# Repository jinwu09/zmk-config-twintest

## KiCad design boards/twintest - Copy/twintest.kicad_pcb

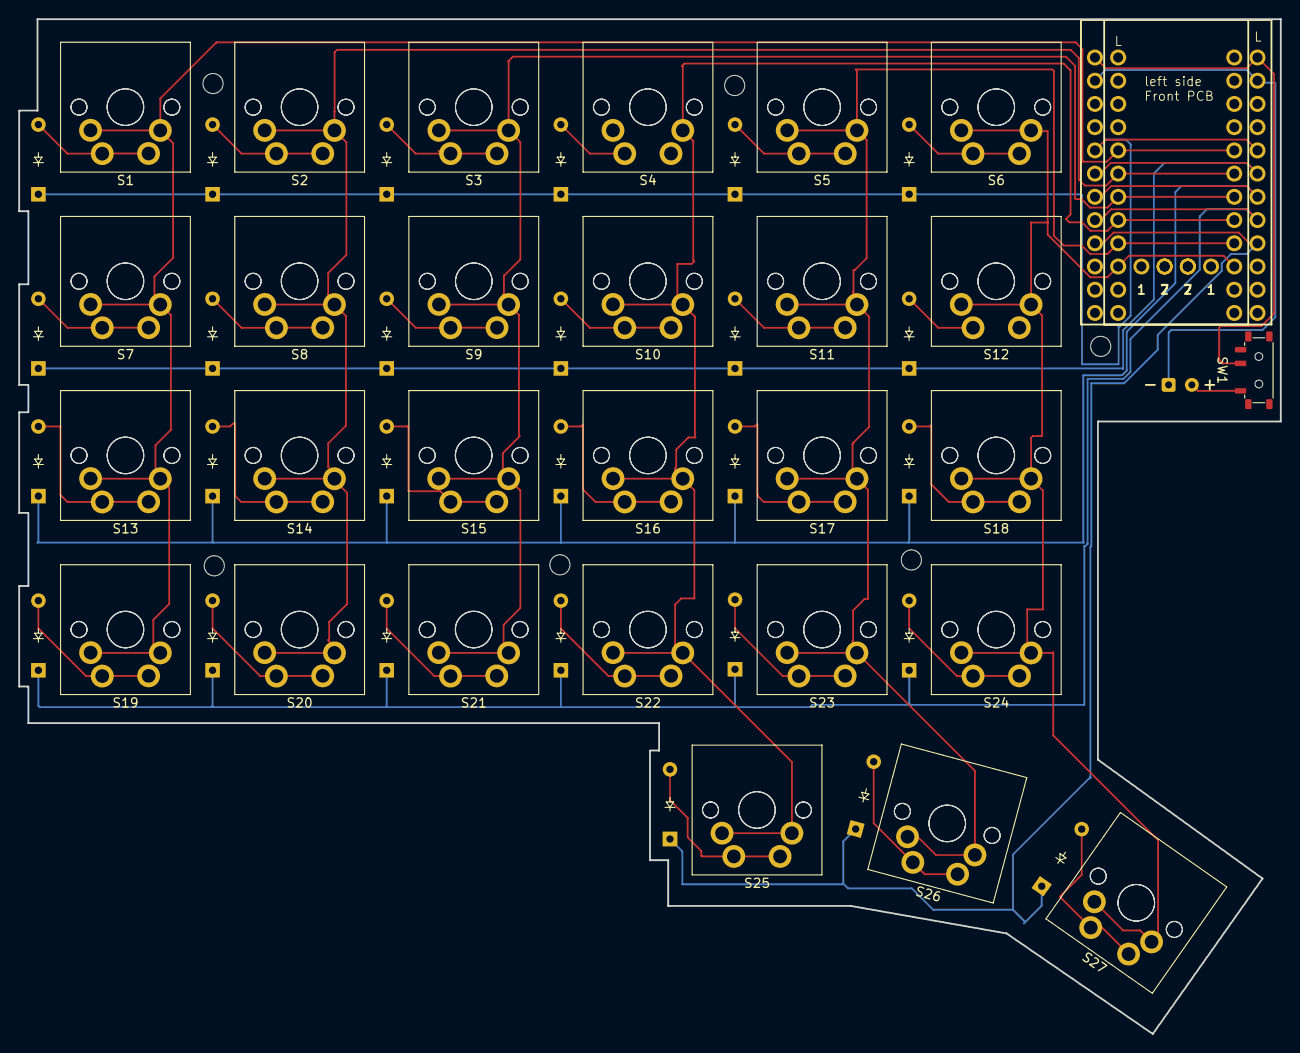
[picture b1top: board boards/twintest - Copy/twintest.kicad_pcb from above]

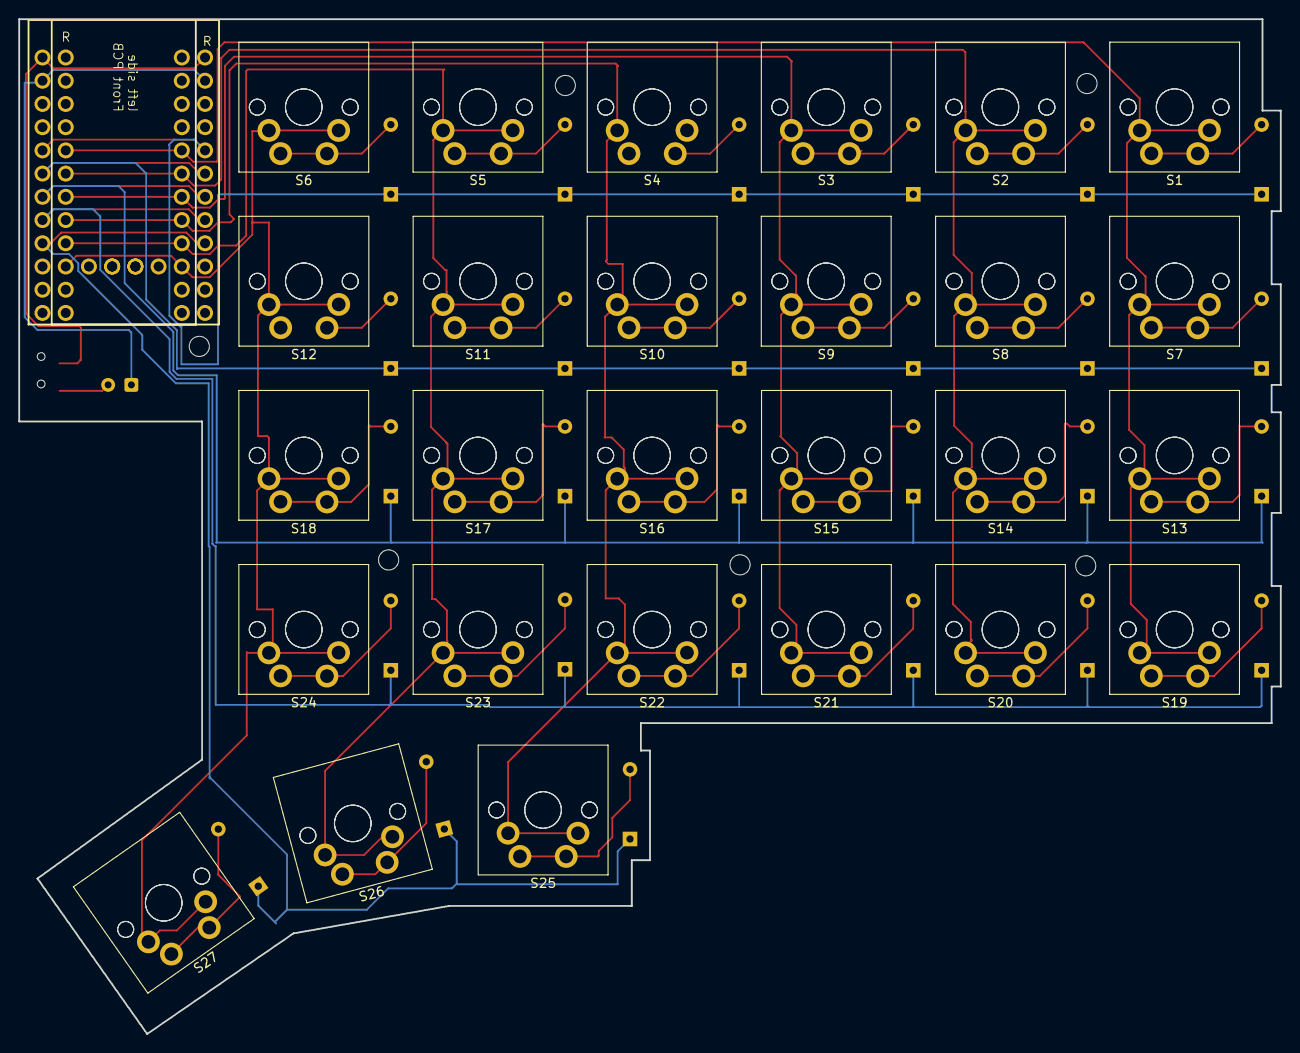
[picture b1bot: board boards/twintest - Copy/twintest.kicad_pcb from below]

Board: 2 copper layers, 138.0 x 111.0 mm, 91 parts (28 on the bottom side), 41 nets.

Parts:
BT2: Battery_Cell; Battery
D1, D2, D3, D4, D5, D6, D7, D8, D9, D10, D11, D12, D13, D14, D15, D16, D17, D18, D19, D20, D21, D22, D23, D24, D25, D26, D27: Diode; Diode_DO-35
H1, H2, H3, H4, H5, H6: Mounting_Hole; Standoff_M2x6mm
S1, S1#2, S2, S2#2, S3, S3#2, S4, S4#2, S5, S5#2, S6, S6#2, S7, S7#2, S8, S8#2, S9, S9#2, S10, S10#2, S11, S11#2, S12, S12#2, S13, S13#2, S14, S14#2, S15, S15#2, S16, S16#2, S17, S17#2, S18, S18#2, S19, S19#2, S20, S20#2, S21, S21#2, S22, S22#2, S23, S23#2, S24, S24#2, S25, S25#2, S26, S26#2, S27, S27#2: Keyswitch; MX_PCB_1.00u
SW1: Switch; Switch_MSK12C02
U1, U2: Nice_Nano_V2

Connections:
unnamed: BT2.1 (+), SW1.2
unnamed: D1.2 (A), S1.2, S1#2.2
unnamed: D2.2 (A), S2.2, S2#2.2
unnamed: D3.2 (A), S3.2, S3#2.2
unnamed: D4.2 (A), S4.2, S4#2.2
unnamed: D5.2 (A), S5.2, S5#2.2
unnamed: D6.2 (A), S6.2, S6#2.2
unnamed: D7.2 (A), S7.2, S7#2.2
unnamed: D8.2 (A), S8.2, S8#2.2
unnamed: D9.2 (A), S9.2, S9#2.2
unnamed: D10.2 (A), S10.2, S10#2.2
unnamed: D11.2 (A), S11.2, S11#2.2
unnamed: D12.2 (A), S12.2, S12#2.2
unnamed: D13.2 (A), S13.2, S13#2.2
unnamed: D14.2 (A), S14.2, S14#2.2
unnamed: D15.2 (A), S15.2, S15#2.2
unnamed: D16.2 (A), S16.2, S16#2.2
unnamed: D17.2 (A), S17.2, S17#2.2
unnamed: D18.2 (A), S18.2, S18#2.2
unnamed: D19.2 (A), S19.2, S19#2.2
unnamed: D20.2 (A), S20.2, S20#2.2
unnamed: D21.2 (A), S21.2, S21#2.2
unnamed: D22.2 (A), S22.2, S22#2.2
unnamed: D23.2 (A), S23.2, S23#2.2
unnamed: D24.2 (A), S24.2, S24#2.2
unnamed: D25.2 (A), S25.2, S25#2.2
unnamed: D26.2 (A), S26.2, S26#2.2
unnamed: D27.2 (A), S27.2, S27#2.2
battery +: SW1.1, U1.24 (B+), U2.24 (B+)
battery -: BT2.2 (-), U1.23 (GND), U2.23 (GND)
collumn 1: S1.1, S1#2.1, S7.1, S7#2.1, S13.1, S13#2.1, S19.1, S19#2.1, U1.5 (2), U2.5 (2)
collumn 2: S2.1, S2#2.1, S8.1, S8#2.1, S14.1, S14#2.1, S20.1, S20#2.1, U1.6 (3), U2.6 (3)
collumn 3: S3.1, S3#2.1, S9.1, S9#2.1, S15.1, S15#2.1, S21.1, S21#2.1, U1.7 (4), U2.7 (4)
collumn 4: S4.1, S4#2.1, S10.1, S10#2.1, S16.1, S16#2.1, S22.1, S22#2.1, S25.1, S25#2.1, U1.8 (5), U2.8 (5)
collumn 5: S5.1, S5#2.1, S11.1, S11#2.1, S17.1, S17#2.1, S23.1, S23#2.1, S26.1, S26#2.1, U1.9 (6), U2.9 (6)
collumn 6: S6.1, S6#2.1, S12.1, S12#2.1, S18.1, S18#2.1, S24.1, S24#2.1, S27.1, S27#2.1, U1.10 (7), U2.10 (7)
row 1: D1.1 (K), D2.1 (K), D3.1 (K), D4.1 (K), D5.1 (K), D6.1 (K), U1.20 (21), U2.20 (21)
row 2: D7.1 (K), D8.1 (K), D9.1 (K), D10.1 (K), D11.1 (K), D12.1 (K), U1.19 (20), U2.19 (20)
row 3: D13.1 (K), D14.1 (K), D15.1 (K), D16.1 (K), D17.1 (K), D18.1 (K), U1.18 (19), U2.18 (19)
row 4: D19.1 (K), D20.1 (K), D21.1 (K), D22.1 (K), D23.1 (K), D24.1 (K), U1.17 (18), U2.17 (18)
row 5: D25.1 (K), D26.1 (K), D27.1 (K), U1.16 (15), U2.16 (15)

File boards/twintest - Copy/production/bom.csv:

Designator,Footprint,Quantity,Value,LCSC Part #
BT2,Battery,1,Battery_Cell,
"D1, D10, D11, D12, D13, D14, D15, D16, D17, D18, D19, D2, D20, D21, D22, D23, D24, D25, D26, D27, D3, D4, D5, D6, D7, D8, D9",Diode_DO-35,27,Diode,
"H1, H2, H3, H4, H5, H6",Standoff_M2x6mm,6,Mounting_Hole,
"S1_2, S1, S10_2, S10, S11_2, S11, S12_2, S12, S13_2, S13, S14_2, S14, S15_2, S15, S16_2, S16, S17_2, S17, S18_2, S18, S19_2, S19, S2_2, S2, S20_2, S20, S21_2, S21, S22_2, S22, S23_2, S23, S24_2, S24, S25_2, S25, S26_2, S26, S27_2, S27, S3_2, S3, S4_2, S4, S5_2, S5, S6_2, S6, S7_2, S7, S8_2, S8, S9_2, S9",MX_PCB_1.00u,54,Keyswitch,
SW1,Switch_MSK12C02,1,Switch,
"U1, U2",Nice_Nano_V2,2,Nice_Nano_V2,

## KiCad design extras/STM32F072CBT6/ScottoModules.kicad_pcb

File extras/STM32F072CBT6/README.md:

# ScottoModules

Two modules based on the STM32F072CBT6 to make integrated MCU PCBs simpler. They're designed to sit between 2 switches on an ortholinear or row-staggered keyboard, column-staggered will require some manual moving to get them to fit correctly.

# Bill of Materials (BOM)

| Quantity | Part                        | LCSC                                                                               |
| -------- | --------------------------- | ---------------------------------------------------------------------------------- |
| 1        | STM32F072CBT6 (LQFP-48_7x7) | [C81720](https://jlcpcb.com/partdetail/Stmicroelectronics-STM32F072CBT6/C81720)    |
| 1        | XC6206 (SOT-23-3L)          | [C5446](https://jlcpcb.com/partdetail/TorexSemicon-XC6206P332MRG/C5446)            |
| 1        | USBLC6-2SC6 (SOT-23-6)      | [C2827654](https://jlcpcb.com/partdetail/TechPublic-USBLC62SC6/C2827654)           |
| 1        | TL3342                      | [C115351](https://jlcpcb.com/partdetail/Alpsalpine-SKQGABE010/C115351)             |
| 1        | USB_C_HRO_TYPE-C-31-M-12    | [C165948](https://jlcpcb.com/partdetail/Korean_HropartsElec-TYPE_C_31_M12/C165948) |
| 2        | 5.1k Resistor (0402)        | [C25905](https://jlcpcb.com/partdetail/26648-0402WGF5101TCE/C25905)                |
| 1        | 10k Resistor (0402)         | [C25744](https://jlcpcb.com/partdetail/26487-0402WGF1002TCE/C25744)                |
| 1        | 500mA Fuse (0603)           | [C210357](https://jlcpcb.com/partdetail/Bourns-MF_FSMF050X2/C210357)               |
| 3        | 1uF Capacitor (0402)        | [C52923](https://jlcpcb.com/partdetail/53938-CL05A105KA5NQNC/C52923)               |
| 1        | 10nF Capacitor (0402)       | [C15195](https://jlcpcb.com/partdetail/15869-CL05B103KB5NNNC/C15195)               |
| 2        | 4.7uF Capacitor (0402)      | [C23733](https://jlcpcb.com/partdetail/24469-CL05A475MP5NRNC/C23733)               |
| 5        | 100nF Capacitor (0402)      | [C307331](https://jlcpcb.com/partdetail/291005-CL05B104KB54PNC/C307331)            |

# Usage

1. The project is setup as a Kicad template, first open Kicad and select "New Project from Template..." from the file menu.

2. Next click the folder icon and navigate to where you saved the `ScottoModules/STM32F072CBT6` folder and open it.

3. Select `ScottoModules (STM32)` and click `OK`.

4. Name your project and save it somewhere.

5. You're now ready to start using ScottoModules!

# Kicad Template Folder

Alternatively, you can save `ScottoModules/STM32F072CBT6` to your Kicad templates folder and not have to manually load it each time.

-   **Mac** - /Users/YOUR_USERNAME/Documents/KiCad/8.0/template/
-   **Windows** - C:\Users\YOUR_USERNAME\Documents\KiCad\8.0\template\

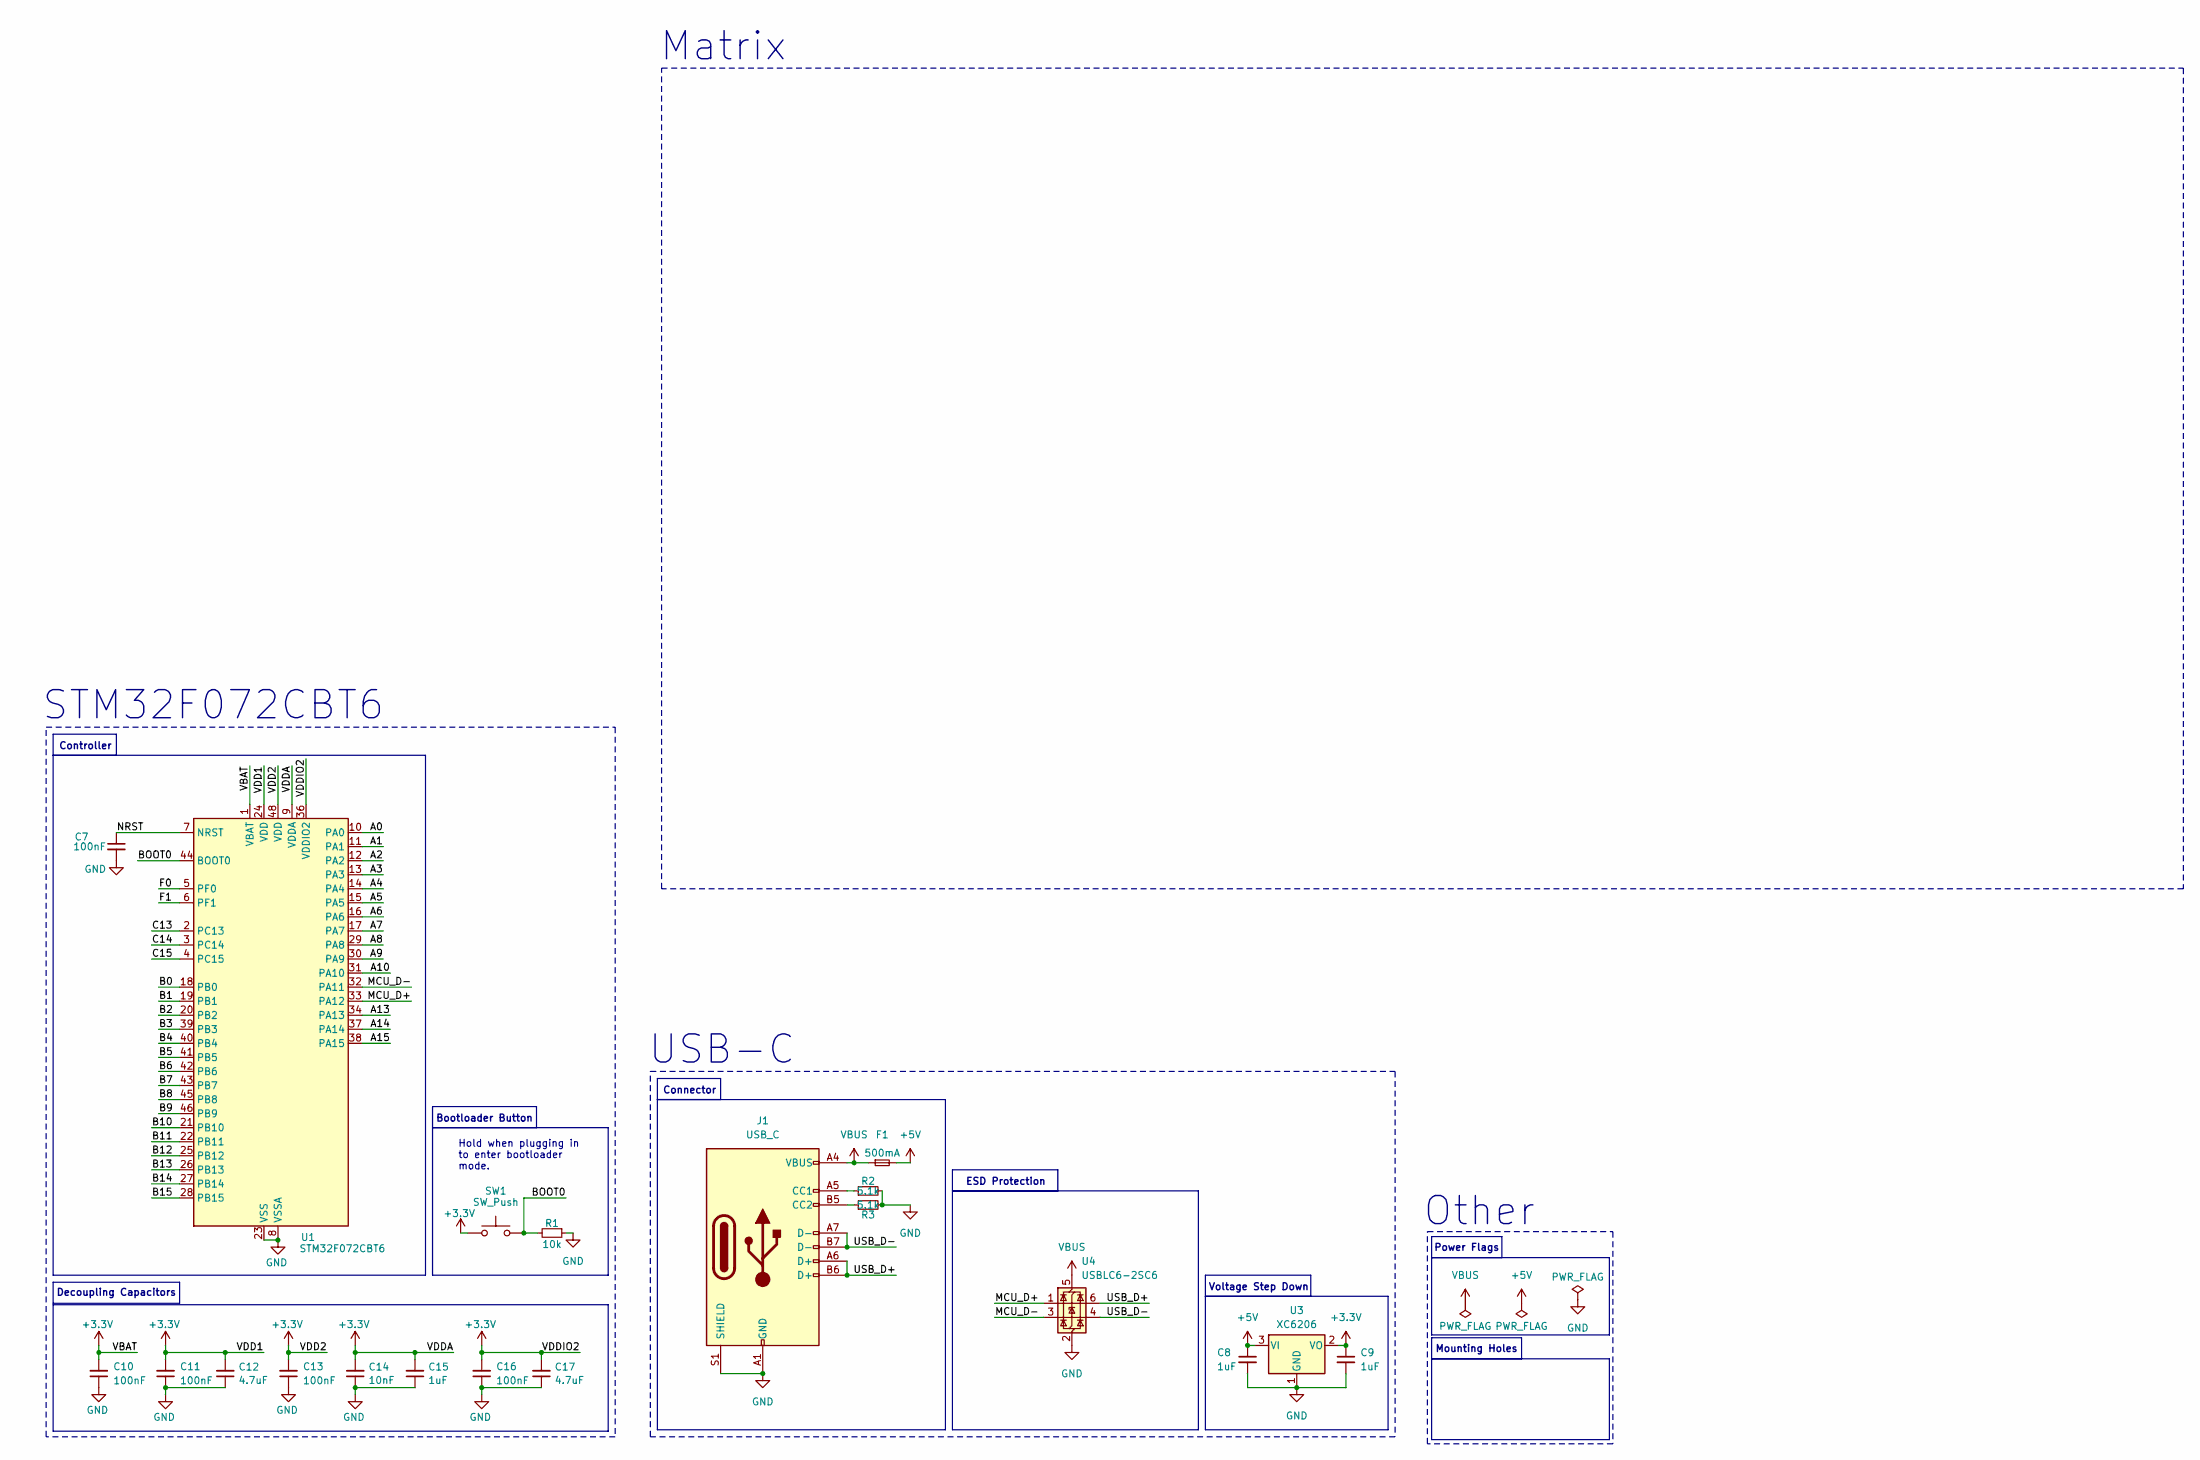
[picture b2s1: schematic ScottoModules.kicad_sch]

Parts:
C7: 100nF; Capacitor_0402; LCSC C307331
C8, C9: 1uF; Capacitor_0402; LCSC C52923
C10, C11, C13, C16: 100nF; Capacitor_0402; MPN CL05B104KB54PNC; LCSC C307331
C12, C17: 4.7uF; Capacitor_0402; MPN CL05A475MP5NRNC; LCSC C23733
C14: 10nF; Capacitor_0402; MPN CL05B103KB5NNNC; LCSC C15195
C15: 1uF; Capacitor_0402; MPN CL05A105KA5NQNC; LCSC C52923
F1: 500mA; Fuse_0603; LCSC C210357
J1: USB_C; USB_C_HRO_TYPE-C-31-M-12; LCSC C165948
R1: 10k; Resistor_0402; LCSC C25744
R2, R3: 5.1k; Resistor_0402; LCSC C25905
SW1: SW_Push; Button_TL3342; LCSC C115351
U1: STM32F072CBT6; Package_LQFP-48_7x7mm_P0.5; LCSC C81720
U3: XC6206; Voltage_SOT-23; LCSC C5446
U4: USBLC6-2SC6; ESD_SOT-23-6; LCSC C2827654

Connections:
+3.3V: C9.1, C10.2, C11.2, C12.2, C13.2, C14.2, C15.2, C16.2, C17.2, SW1.1, U1.1 (VBAT), U1.9 (VDDA), U1.24 (VDD), U1.36 (VDDIO2), U1.48 (VDD), U3.2 (VO)
+5V: C8.1, F1.2, U3.3 (VI)
/A0: U1.10 (PA0)
/A1: U1.11 (PA1)
/A2: U1.12 (PA2)
/A3: U1.13 (PA3)
/A4: U1.14 (PA4)
/A5: U1.15 (PA5)
/A6: U1.16 (PA6)
/A7: U1.17 (PA7)
/A8: U1.29 (PA8)
/A9: U1.30 (PA9)
/A10: U1.31 (PA10)
/A13: U1.34 (PA13)
/A14: U1.37 (PA14)
/A15: U1.38 (PA15)
/B0: U1.18 (PB0)
/B1: U1.19 (PB1)
/B2: U1.20 (PB2)
/B3: U1.39 (PB3)
/B4: U1.40 (PB4)
/B5: U1.41 (PB5)
/B6: U1.42 (PB6)
/B7: U1.43 (PB7)
/B8: U1.45 (PB8)
/B9: U1.46 (PB9)
/B10: U1.21 (PB10)
/B11: U1.22 (PB11)
/B12: U1.25 (PB12)
/B13: U1.26 (PB13)
/B14: U1.27 (PB14)
/B15: U1.28 (PB15)
/BOOT0: R1.2, SW1.2, U1.44 (BOOT0)
/C13: U1.2 (PC13)
/C14: U1.3 (PC14)
/C15: U1.4 (PC15)
/F0: U1.5 (PF0)
/F1: U1.6 (PF1)
/MCU_D+: U1.33 (PA12), U4.1 (I/O1)
/MCU_D-: U1.32 (PA11), U4.3 (I/O2)
/NRST: C7.1, U1.7 (NRST)
/USB_D+: J1.A6 (D+), J1.B6 (D+), U4.6 (I/O1)
/USB_D-: J1.A7 (D-), J1.B7 (D-), U4.4 (I/O2)
GND: C7.2, C8.2, C9.2, C10.1, C11.1, C12.1, C13.1, C14.1, C15.1, C16.1, C17.1, J1.A1 (GND), J1.A12 (GND), J1.B1 (GND), J1.B12 (GND), J1.S1 (SHIELD), R1.1, R2.2, R3.2, U1.8 (VSSA), U1.23 (VSS), U1.35 (VSS), U1.47 (VSS), U3.1 (GND), U4.2 (GND)
unnamed: J1.A5 (CC1), R2.1
unnamed: J1.B5 (CC2), R3.1
VBUS: F1.1, J1.A4 (VBUS), J1.A9 (VBUS), J1.B4 (VBUS), J1.B9 (VBUS), U4.5 (VBUS)

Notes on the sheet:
Hold when plugging in to enter bootloader mode.
STM32F072CBT6
USB-C
Mounting Holes
Decoupling Capacitors
Controller
ESD Protection
Power Flags
Voltage Step Down
Other
Bootloader Button
Matrix
Connector

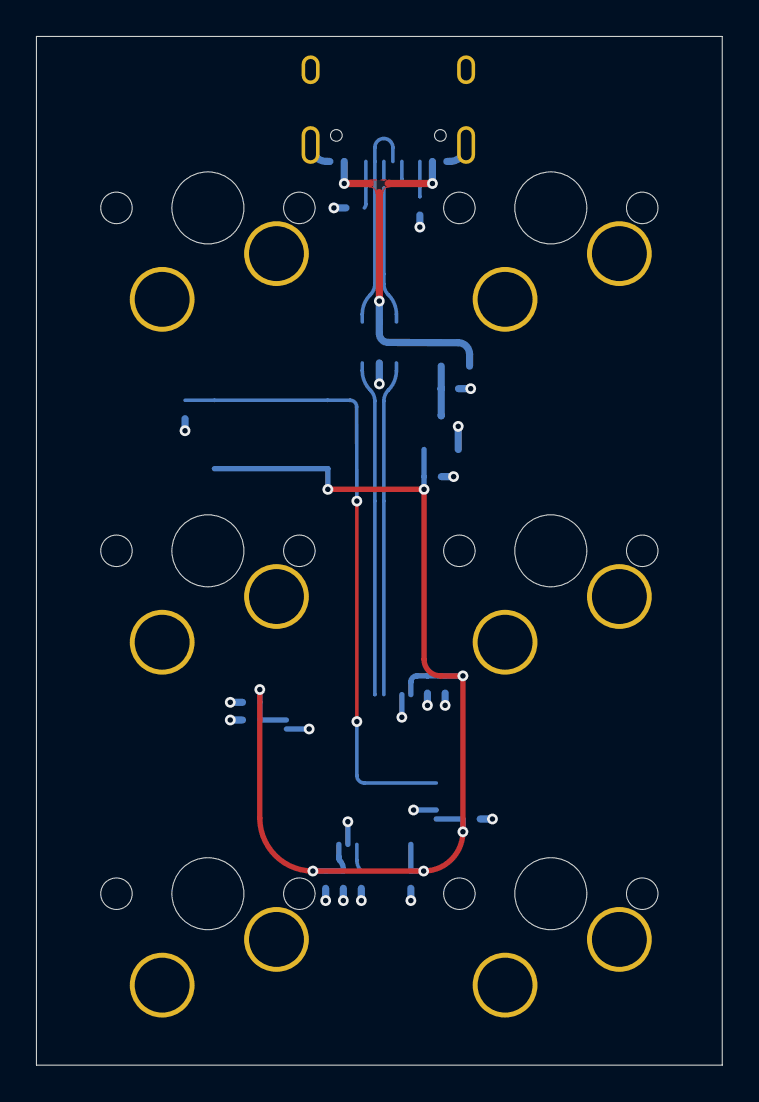
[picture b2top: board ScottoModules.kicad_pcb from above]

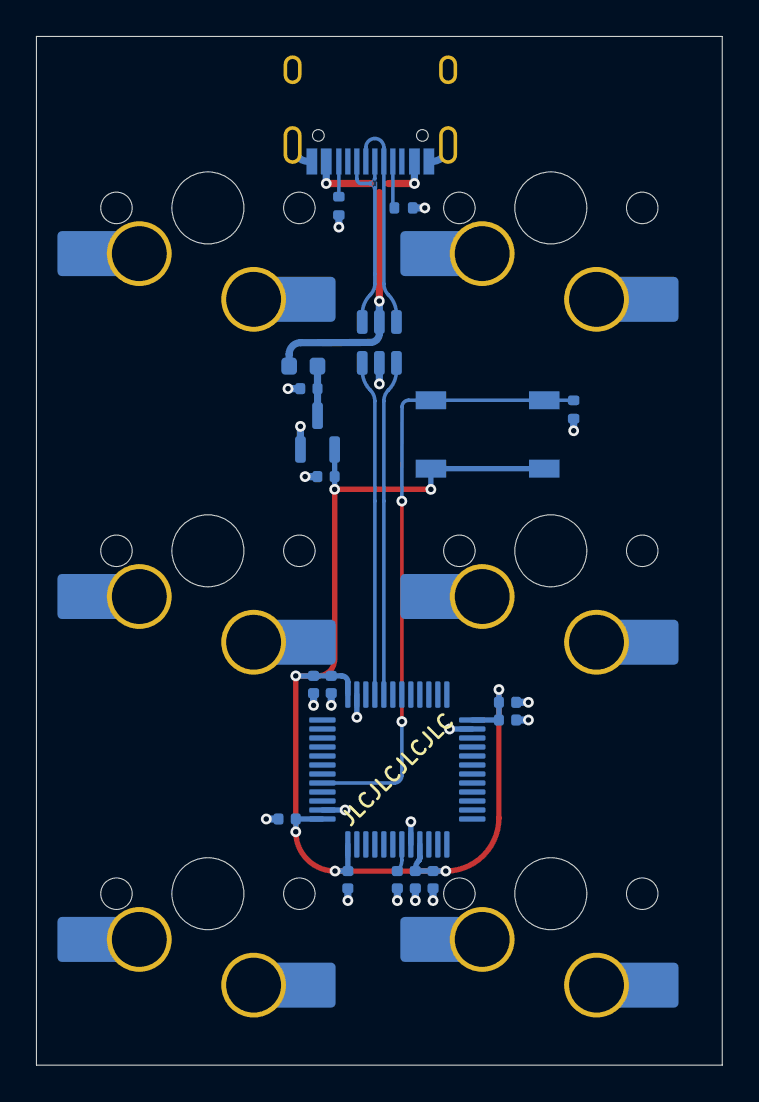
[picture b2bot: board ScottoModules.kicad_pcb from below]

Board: 4 copper layers, 38.1 x 57.2 mm, 20 parts (20 on the bottom side), 12 nets.

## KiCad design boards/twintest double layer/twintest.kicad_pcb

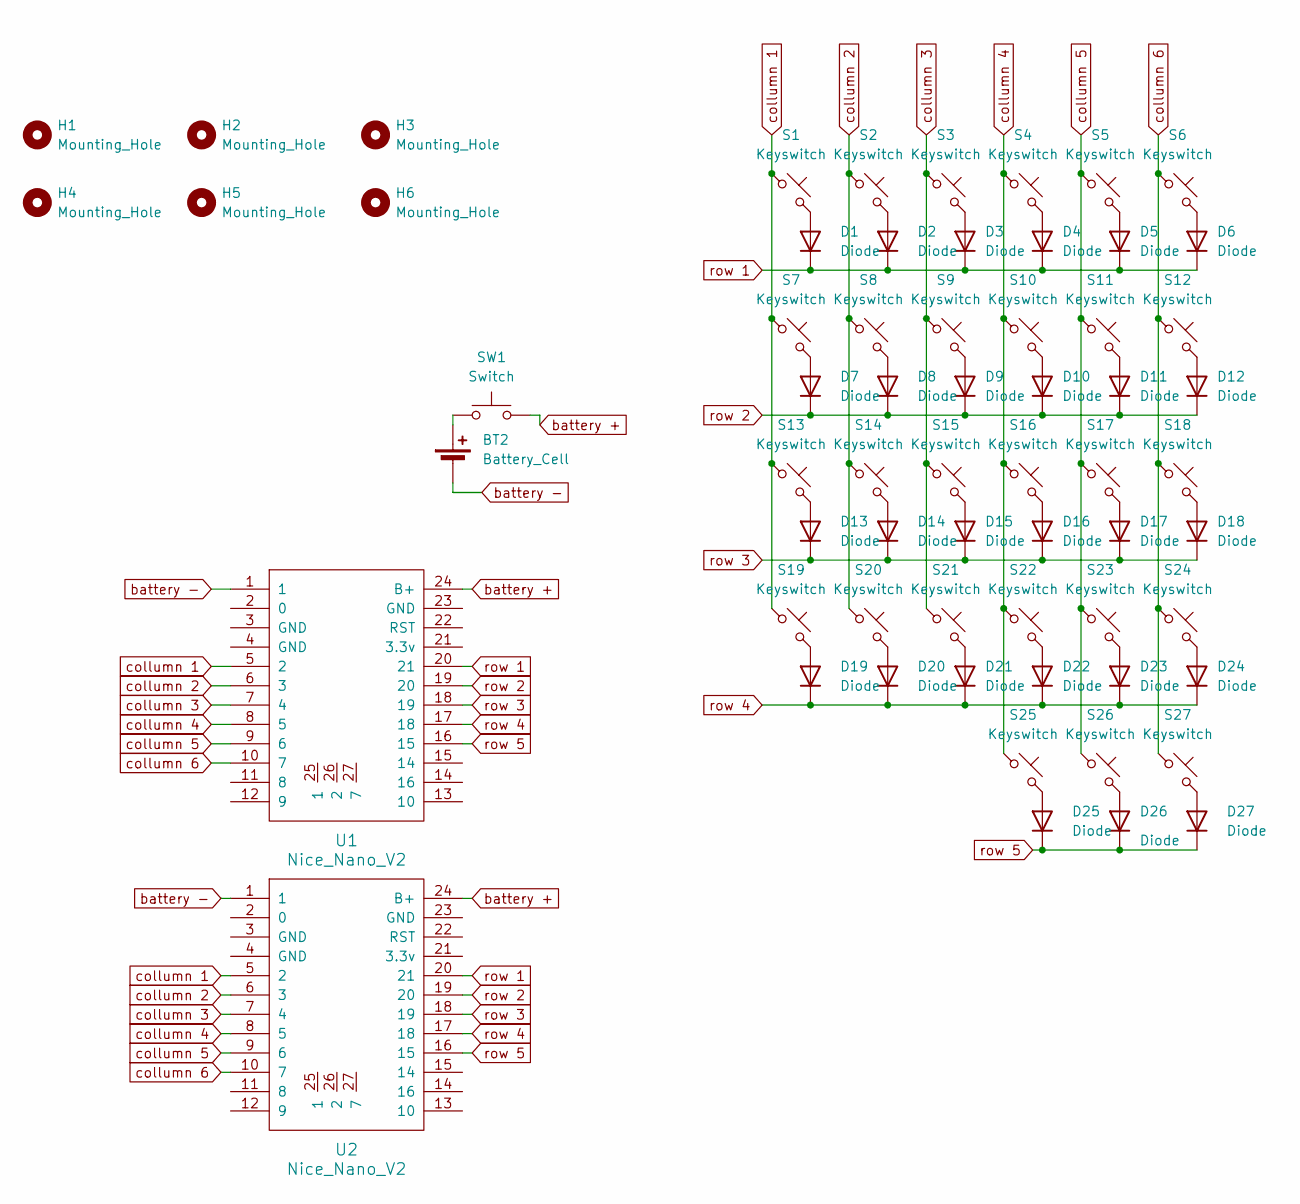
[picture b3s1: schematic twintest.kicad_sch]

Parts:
BT2: Battery_Cell; Battery
D1, D2, D3, D4, D5, D6, D7, D8, D9, D10, D11, D12, D13, D14, D15, D16, D17, D18, D19, D20, D21, D22, D23, D24, D25, D26, D27: Diode; Diode_DO-35
H1, H2, H3, H4, H5, H6: Mounting_Hole; Standoff_M2x6mm
S1, S2, S3, S4, S5, S6, S7, S8, S9, S10, S11, S12, S13, S14, S15, S16, S17, S18, S19, S20, S21, S22, S23, S24, S25, S26, S27: Keyswitch; MX_PCB_1.00u
SW1: Switch; Switch_MSK12C02
U1, U2: Nice_Nano_V2

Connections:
unnamed: D1.2 (A), S1.2
unnamed: D2.2 (A), S2.2
unnamed: D3.2 (A), S3.2
unnamed: D4.2 (A), S4.2
unnamed: D5.2 (A), S5.2
unnamed: D6.2 (A), S6.2
unnamed: D7.2 (A), S7.2
unnamed: D8.2 (A), S8.2
unnamed: D9.2 (A), S9.2
unnamed: D10.2 (A), S10.2
unnamed: D11.2 (A), S11.2
unnamed: D12.2 (A), S12.2
unnamed: D13.2 (A), S13.2
unnamed: D14.2 (A), S14.2
unnamed: D15.2 (A), S15.2
unnamed: D16.2 (A), S16.2
unnamed: D17.2 (A), S17.2
unnamed: D18.2 (A), S18.2
unnamed: D19.2 (A), S19.2
unnamed: D20.2 (A), S20.2
unnamed: D21.2 (A), S21.2
unnamed: D22.2 (A), S22.2
unnamed: D23.2 (A), S23.2
unnamed: D24.2 (A), S24.2
unnamed: D25.2 (A), S25.2
unnamed: D26.2 (A), S26.2
unnamed: D27.2 (A), S27.2
battery -: BT2.2 (-), U1.1, U2.1
collumn 1: S1.1, S7.1, S13.1, S19.1, U1.5 (2), U2.5 (2)
collumn 2: S2.1, S8.1, S14.1, S20.1, U1.6 (3), U2.6 (3)
collumn 3: S3.1, S9.1, S15.1, S21.1, U1.7 (4), U2.7 (4)
collumn 4: S4.1, S10.1, S16.1, S22.1, S25.1, U1.8 (5), U2.8 (5)
collumn 5: S5.1, S11.1, S17.1, S23.1, S26.1, U1.9 (6), U2.9 (6)
collumn 6: S6.1, S12.1, S18.1, S24.1, S27.1, U1.10 (7), U2.10 (7)
row 1: D1.1 (K), D2.1 (K), D3.1 (K), D4.1 (K), D5.1 (K), D6.1 (K), U1.20 (21), U2.20 (21)
row 2: D7.1 (K), D8.1 (K), D9.1 (K), D10.1 (K), D11.1 (K), D12.1 (K), U1.19 (20), U2.19 (20)
row 3: D13.1 (K), D14.1 (K), D15.1 (K), D16.1 (K), D17.1 (K), D18.1 (K), U1.18 (19), U2.18 (19)
row 4: D19.1 (K), D20.1 (K), D21.1 (K), D22.1 (K), D23.1 (K), D24.1 (K), U1.17 (18), U2.17 (18)
row 5: D25.1 (K), D26.1 (K), D27.1 (K), U1.16 (15), U2.16 (15)

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
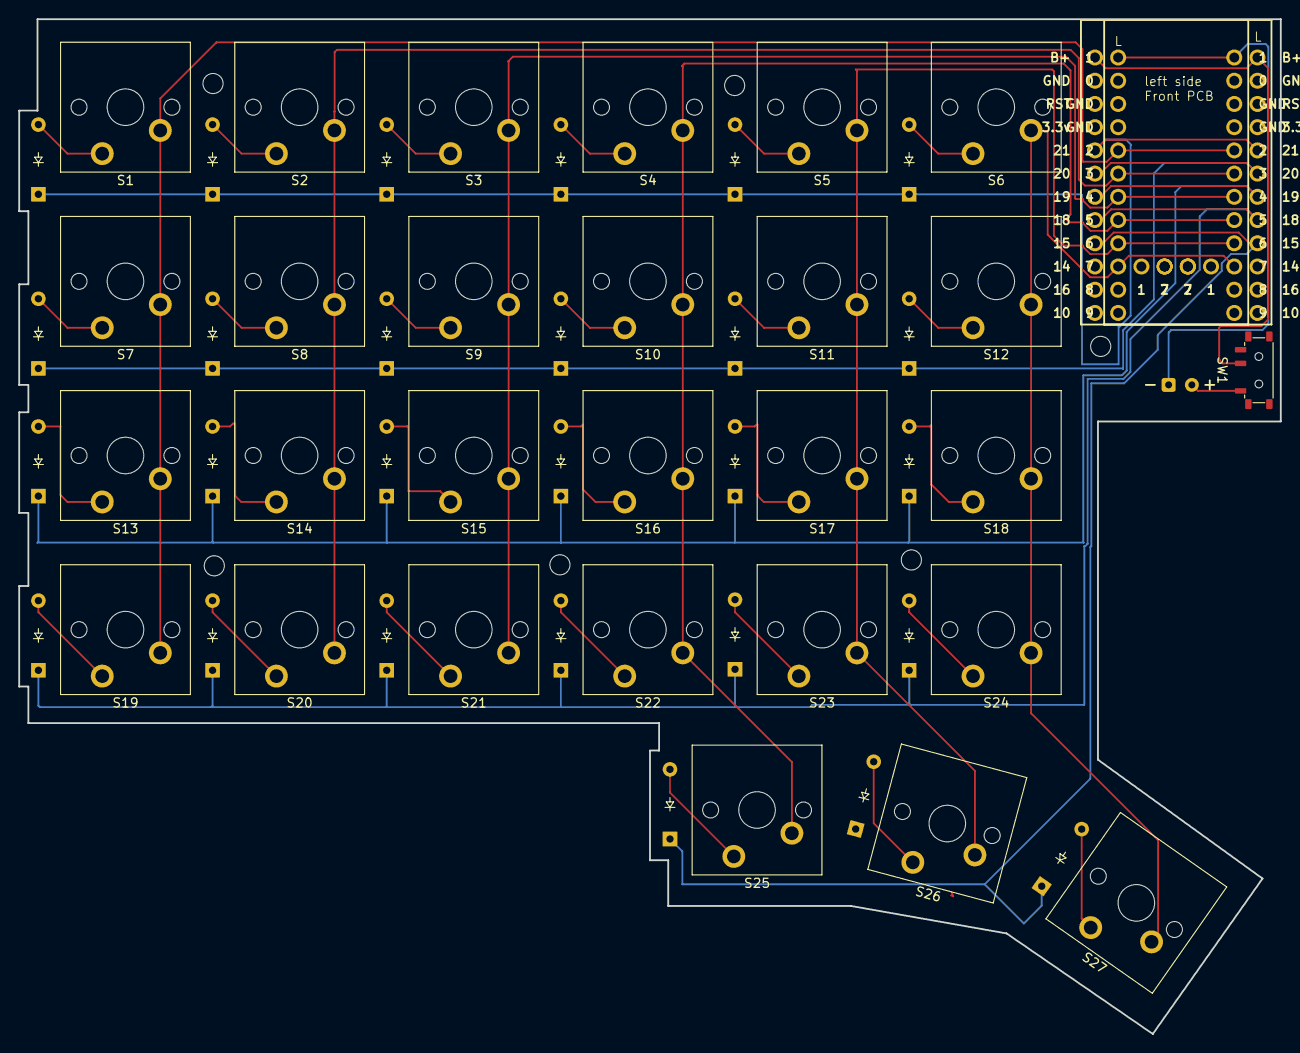
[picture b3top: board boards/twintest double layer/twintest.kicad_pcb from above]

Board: 2 copper layers, 138.0 x 111.0 mm, 64 parts (1 on the bottom side), 41 nets.

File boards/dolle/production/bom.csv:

Designator,Footprint,Quantity,Value,LCSC Part #
BT1,Battery,1,Battery_Cell,
"D1, D10, D11, D12, D13, D14, D15, D16, D17, D18, D19, D2, D20, D21, D22, D23, D24, D25, D26, D27, D28, D29, D3, D4, D5, D6, D7, D8, D9",Diode_DO-35,29,Diode,
J1,PinHeader_1x06_P2.54mm_Vertical,1,trackball,
"S1_4, S1_3, S1_2, S1, S10_2, S10, S11_4, S11_3, S11_2, S11, S12_2, S12, S17_2, S17, S18_2, S18, S19_2, S19, S20_2, S20, S25_2, S25, S26_2, S26, S27_2, S27, S28_2, S28, S3_2, S3, S33_2, S33, S34_2, S34, S35_2, S35, S36_2, S36, S41_2, S41, S42_2, S42, S43_2, S43, S44_2, S44, S49_2, S49, S5_2, S5, S51_2, S51, S53_2, S53, S55_2, S55, S7_2, S7, S9_2, S9",Choc_V1V2,60,Keyswitch,
"S13_2, S13, S14_2, S14, S15_4, S15_3, S15_2, S15, S16_2, S16, S2_4, S2_3, S2_2, S2, S21_2, S21, S22_2, S22, S23_2, S23, S24_2, S24, S29_2, S29, S30_2, S30, S31_2, S31, S32_2, S32, S37_2, S37, S38_2, S38, S39_2, S39, S4_2, S4, S40_2, S40, S45_2, S45, S46_2, S46, S47_2, S47, S48_2, S48, S50_2, S50, S52_2, S52, S54_2, S54, S56_2, S56, S6_2, S6, S8_2, S8",MX_PCB_1.00u,60,Keyswitch,
"SW1_2, SW1",Switch_MSK12C02,2,Switch,
SW3,RotaryEncoder_Alps_EC11E_Vertical_H20mm,1,RotaryEncoder_Switch_MP,
SW4,SW_PUSH_6mm,1,SW_Push,
"U1_2, U1",Nice_Nano_V2,2,Nice_Nano_V2,

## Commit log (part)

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2024-11-04 Initial User Config.
2024-11-04 test push
2024-11-04 lels
2024-11-04 lels again
2024-11-04 reeee
2024-11-04 reee
2024-11-04 damn
2024-11-04 reset
2024-11-04 z for what?
2024-11-04 z capital
2024-11-04 JUST MAKE IT INTO matrix
2024-11-04 meow
2024-11-04 physical layout
2024-11-04 idk what to do
2024-11-04 test without transform
2024-11-05 bring back the matrix transform
2024-11-05 testing
2024-11-05 welp
2024-11-05 test
2024-12-20 pcb board
2025-01-10 just worrk
2025-01-10 wewewe
2025-01-10 teest
2025-01-10 reeeee again
2025-01-10 remap
2025-01-10 include out
2025-01-12 updaattte
2025-01-12 with transform
2025-01-12 upddddddd
2025-01-12 save
2025-01-16 here iit is
2025-01-16 gaming updatw
2025-01-16 update layer
2025-01-16 typo
2025-01-16 update layer
2025-01-16 alt f4
2025-01-16 fiix
2025-01-17 param fix
2025-01-17 check
2025-01-18 hold tap fiix
2025-01-21 wireless
2025-01-21 test ble
2025-02-17 update new keyboard layout
2025-02-17 run actionn
2025-02-17 Revert "test"
    This reverts commit fa0f28e978b9e7bd64d901a5554b8d8d81d88973.
2025-02-17 init
2025-02-17 layout fix
2025-02-17 build fix
2025-02-17 update build
2025-02-17 change shield name
2025-02-17 change name
2025-02-17 promicro pin layout
2025-02-17 lels lezgo
2025-02-17 1 try
2025-02-17 keymap
2025-02-21 mouse keys
2025-02-21 mouse click
2025-03-04 errereer
2025-03-24 feat(keymap): update key bindings for Dolle layout
    Replace ESC with GRAVE in the default layer for better access.
    Add BACKSPACE to the last row of the default layer for improved
    functionality. Update the Layer_Handler to include BACKSLASH
    for enhanced usability. These changes aim to optimize the
    keyboard layout for user efficiency and comfort.
2025-03-26 fix(config): update keyboard name and add newline inconfig
    Change the default keyboard name from "Dolle" to "Dolles" to better
    reflect the product branding. Add a missing newline at the end of the
    Kconfig.defconfig file for proper formatting and to adhere to coding
    standards.
2025-03-26 fix(config): update keyboard name and clean up Kconfig
    Shorten the default keyboard name from "Dolles" to "Dolle" to meet
    the character limit requirement. Clean up the Kconfig file by
    removing unnecessary whitespace and ensuring proper formatting.
2025-03-31 fix(keymap): correct syntax for macro tap binding
    Update the Dolle keymap to fix the syntax of the macro tap binding.
    Replace the comma with a semicolon to ensure proper parsing and
    functionality of the keymap configuration. This change enhances
    the stability of the keymap and prevents potential errors during
    compilation.
2025-03-31 refactor: comment out unused macro bindings in keymap
    Comment out the unused macro bindings for Bluetooth selection and
    output in the Dolle keymap. This change improves code clarity and
    prevents potential confusion regarding unused features.
2025-03-31 feat(keymap): update Dolle keymap for improved functionality
    Corrects the key binding for the left Windows key to ensure it
    functions properly. Adds a new behavior macro for Bluetooth
    switching, enhancing the keymap's capabilities. Updates the
    connection bindings to reflect the new Bluetooth switch
    configuration, improving overall usability and performance.
2025-03-31 fix: correct binding names and improve macro behavior
    Update the keymap to use consistent naming for Bluetooth switch
    bindings by changing `btsw` to `bt_sw`. Enhance the macro behavior
    by uncommenting additional macro tap bindings for better
    functionality. These changes ensure clarity and improve the
    overall performance of the keymap.
2025-03-31 fix: add missing comma in Dolle keymap bindings
    Add a missing comma in the bindings section of the Dolle keymap
    ensure proper syntax and prevent potential parsing errors. This
    change improves the overall stability and functionality of the
    keyboard configuration.
2025-03-31 refactor: update Dolle keymap bindings for clarity
    Remove unused macro tap bindings in the Dolle keymap to improve
    readability and maintainability. This change simplifies the
    configuration by focusing on the relevant macro parameters.
2025-03-31 refactor: update Dolle keymap for improved Bluetooth handling
    Adjust the connection bindings in the Dolle keymap to enhance
    Bluetooth functionality. Change the output from OUT_USB to OUT_BLE
    for better compatibility with Bluetooth devices. This improves the
    overall user experience by ensuring proper device communication
    and functionality.
2025-03-31 fix(keymap): restore BT_SEL macro binding in Dolle keymap
    Restores the BT_SEL macro binding in the Dolle keymap to ensure
    proper functionality of the Bluetooth selection feature. This
    change corrects a previous omission that could lead to
    inconsistent behavior during usage.
2025-03-31 fix(keymap): enable Bluetooth and output macros
    Uncomment Bluetooth and output macros in the Dolle keymap to
    activate their functionality. This change enhances the
    keyboard's capabilities by allowing users to utilize these
    macros effectively.
2025-03-31 fix(keymap): correct syntax in Dolle keymap configuration
    Adjust the closing brace in the Dolle keymap file to ensure proper
    syntax. This change resolves potential parsing issues and improves
    the overall stability of the keymap configuration.
2025-03-31 refactor: change macro_press to macro_tap in keymap
    Update the keymap for the Dolle shield to replace
    macro_press macro_tap better functionality.
    change enhances the of the
    bindings for Bluetooth selection and output.
2025-03-31 feat(keymap): update Bluetooth key bindings for Dolle shield
    Adjusts the keymap for the Dolle shield to include Bluetooth selection
    bindings. This change enhances user experience by allowing direct
    selection of Bluetooth devices, improving accessibility and
    functionality in gaming and default modes.
2025-03-31 fix(board): correct binding-cells syntax in Dolle keymap
    Update the Dolle keymap to fix the syntax for the
    #binding-cells property. This change ensures proper
    parsing of the device tree, improving functionality
    and compatibility with the ZMK framework.
2025-03-31 fix: correct typo in Dolle keymap behavior compatibility
    Correct the spelling of "behavior" in the Dolle keymap file to ensure
    proper compatibility with the ZMK framework. This change resolves
    potential issues with keymap functionality.
2025-03-31 fix(keymap): update key bindings for improved functionality
    Adjusts key bindings in the Dolle keymap to enhance usability.
    Replaces LWIN with LSHIFT for better access to modifier keys and
    ensures consistent behavior across layers. This change aims to
    streamline user experience and improve typing efficiency.
2025-03-31 refactor: remove unused Bluetooth switch behavior
    Eliminate the Bluetooth switch behavior definition from the Dolle
    keymap file. This change simplifies the configuration by removing
    unnecessary code, improving readability and maintainability.
2025-04-04 feat(keymap): add symbol layer and update default layers
    Add a new SYMBOL layer to the Dolle keymap for additional
    symbol bindings. Update the DEFAULT and GAMING layers to
    improve key assignments, enhancing usability and
    functionality for users.
2025-04-05 feat(keymap): add SYMBOL layer for enhanced functionality
    Add a new SYMBOL layer to the Dolle keymap to improve user
    experience by providing additional key options. Update the
    keymap to include the SYMBOL layer in the relevant sections,
    allowing for more versatile key combinations and better
    accessibility during use.
2025-04-05 fix(keymap): update Dolle keymap for improved functionality
    Adjust the key bindings in the Dolle keymap to enhance user experience.
    Replace the backslash key with a more accessible option and ensure
    consistent behavior in the SYMBOL layer by modifying the
    transitional key. These changes aim to streamline input and
    improve overall usability.
2025-04-05 GitButler Workspace Commit
    This is a merge commit the virtual branches in your workspace.
    Due to GitButler managing multiple virtual branches, you cannot switch back and
    forth between git branches and virtual branches easily.
    If you switch to another branch, GitButler will need to be reinitialized.
    If you commit on this branch, GitButler will throw it away.
    Here are the branches that are currently applied:
2025-04-09 Merge pull request #1 from jinwu09/j-branch-1
    j-branch-1
2025-04-09 feat(keymap): update key definitions and add NUMROW layer
    Refactor key definitions in Dolle.keymap to improve clarity and
    functionality. Replace CONNECTION and SYMBOL definitions with
    NUMROW and updated CONNECTION values. Add a new NUMROW layer
    with specific bindings for number keys, enhancing the keyboard's
    capabilities for numeric input.
2025-04-09 fix(keymap): resolve merge conflicts and update bindings
    Resolve merge conflicts in Dolle.keymap and ensure consistent key
    bindings. Update the layer transitions to include NUMROW for better
    functionality. Add a newline at the end of TwinTest.keymap for
    conformance with file standards.
2025-04-09 fix: update keymap bindings for improved functionality
    Adjust keymap bindings in Dolle.keymap to enhance usability.
    Add `kp PERIOD` to the number pad layout and correct the
    placement of the `&mo HANDLER` layer. These changes aim to
    streamline user interactions and improve overall keyboard
    performance.
2025-04-09 GitButler Workspace Commit
    This is a merge commit the virtual branches in your workspace.
    Due to GitButler managing multiple virtual branches, you cannot switch back and
    forth between git branches and virtual branches easily.
    If you switch to another branch, GitButler will need to be reinitialized.
    If you commit on this branch, GitButler will throw it away.
    Here are the branches that are currently applied:
2025-06-21 edit gpio
2025-06-21 build
2025-06-21 pi edit
2025-10-20 update name to dolle slim
2025-10-20 a little fix strings
2025-10-20 WIPorkflow
2025-10-20 yes pls
2025-10-21 change pin out
2025-11-07 update keymap
2025-11-11 update added function key
2025-11-11 dolle system
2025-11-11 added minus
2025-11-11 play pause function
2025-11-26 studio config
2025-11-26 zmk studio update config
2025-11-26 studio added keys
2025-11-26 update studio include
2025-11-26 update studio keys layout
2025-11-26 update studio layout
2025-11-26 reee studio layout update
2025-11-26 studio unlock
2025-11-26 update keymap and fixes
2026-04-08 init lazygit
2026-05-13 change board
2026-05-13 change boars
2026-05-13 use v0.2
